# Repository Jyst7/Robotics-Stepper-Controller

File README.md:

# Robotics-Stepper-Controller

This project is a motor controller board and a cycloidal gearbox. It is designed around the esp32 s3 and can handle up to 6 nema 23's using dm542's.

## Main features

- ESP32 S3: allows for wifi and bluetooth connectivity aswell as allows programming using arduino ide

- up to 6 motors: allows for using up to 60 motors through the dm542 motor driver

- up to 8 inputs: allows for some electrically isolated inputs for limit switches probes, etc

- Sd card: not to sure what to use it for at the moment but its useful to have

- 3d printed cycloidal reducer: 1:10 ratio cycloidal gearbox designed to mount to a Keling KL23H276-30-4A stepper motor

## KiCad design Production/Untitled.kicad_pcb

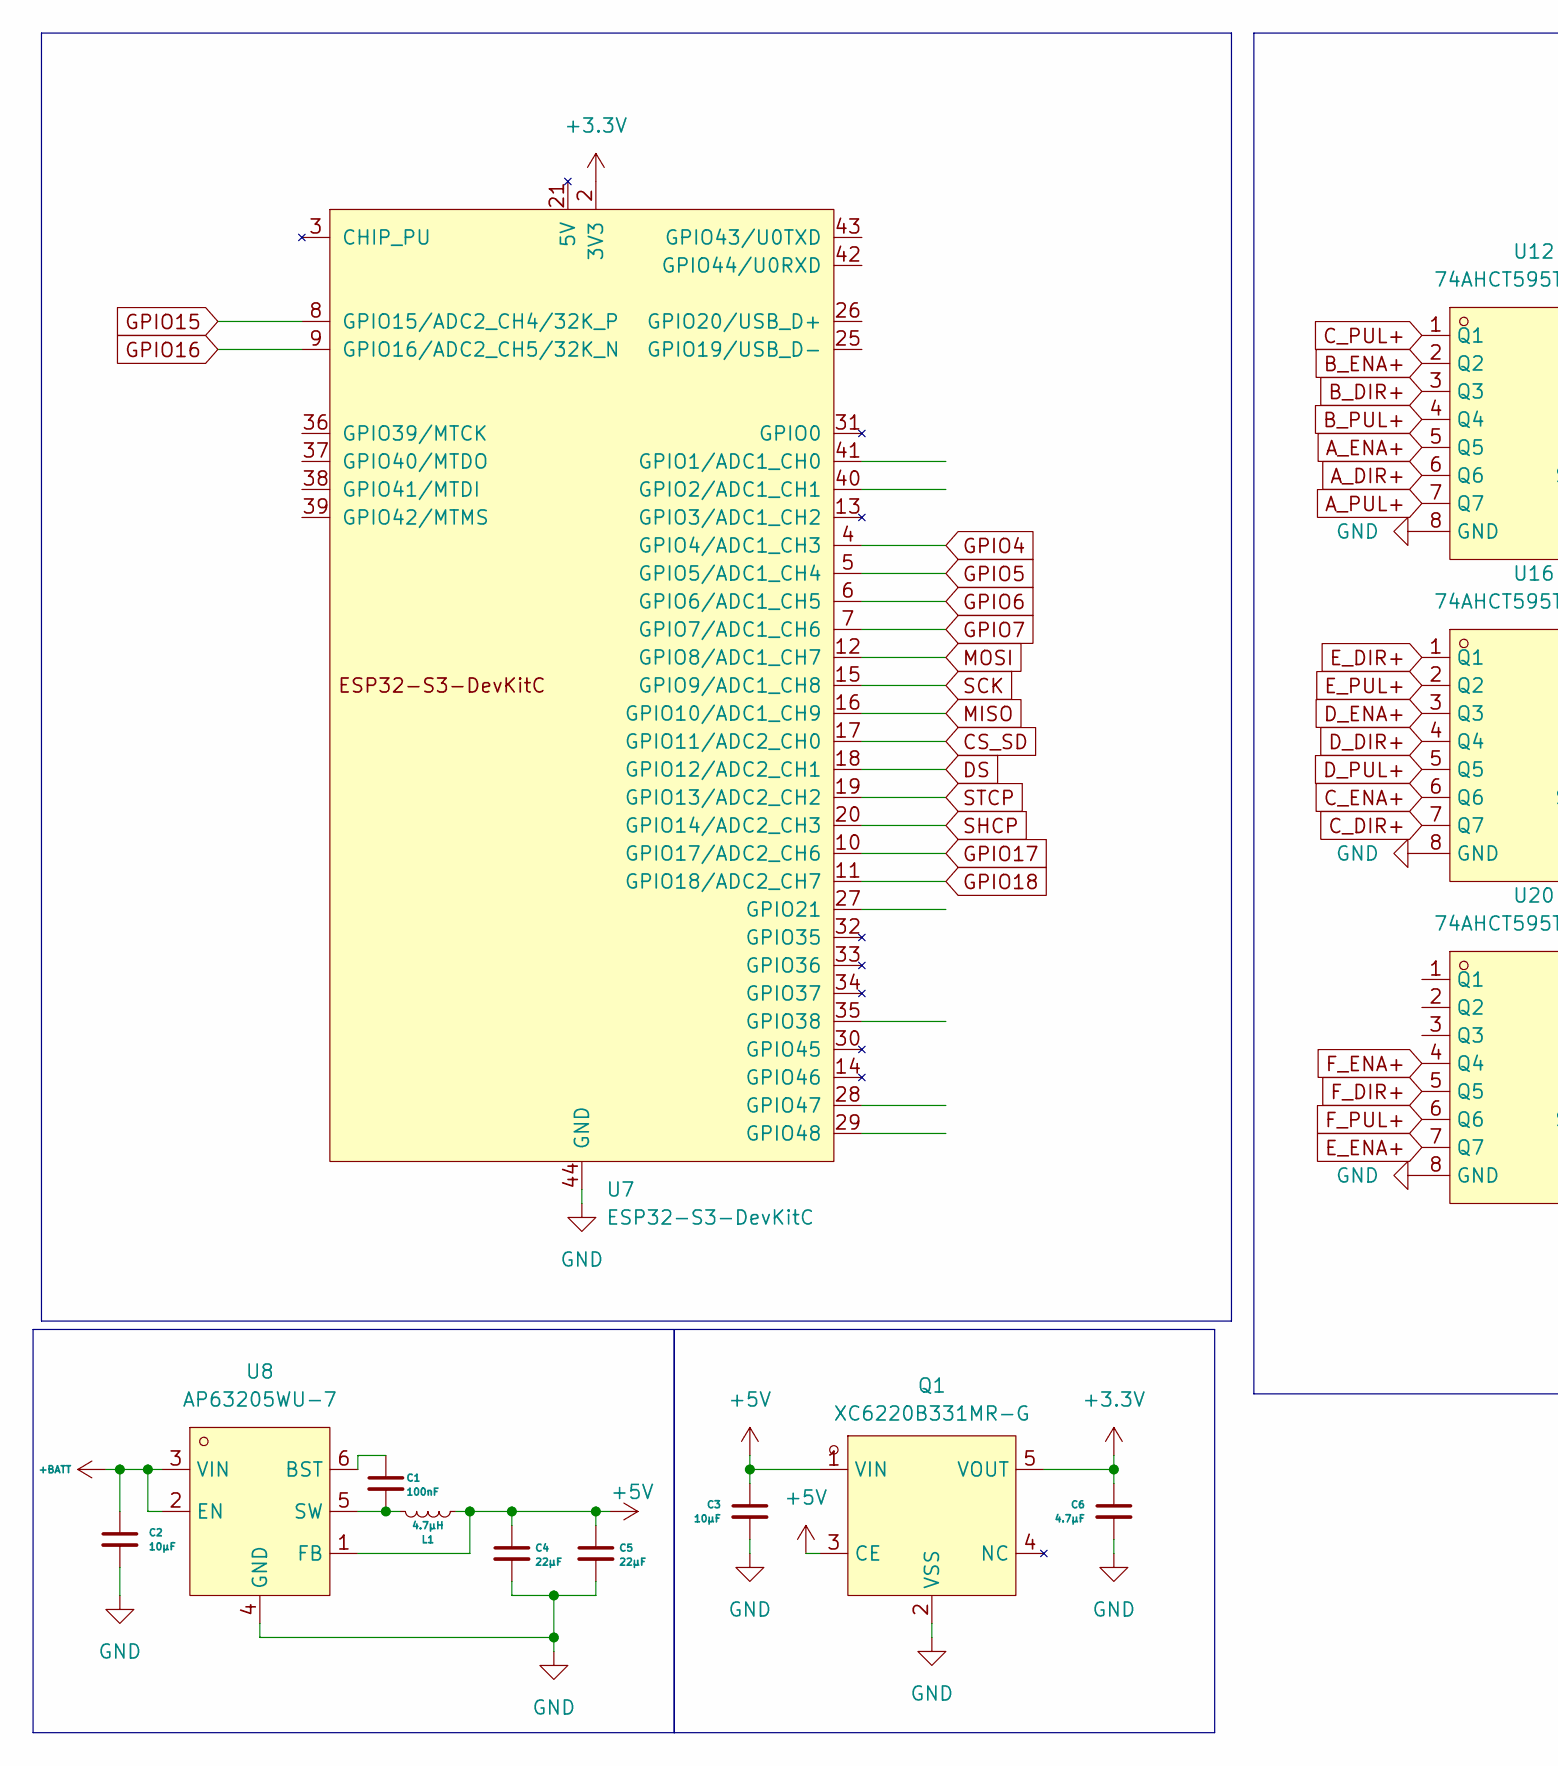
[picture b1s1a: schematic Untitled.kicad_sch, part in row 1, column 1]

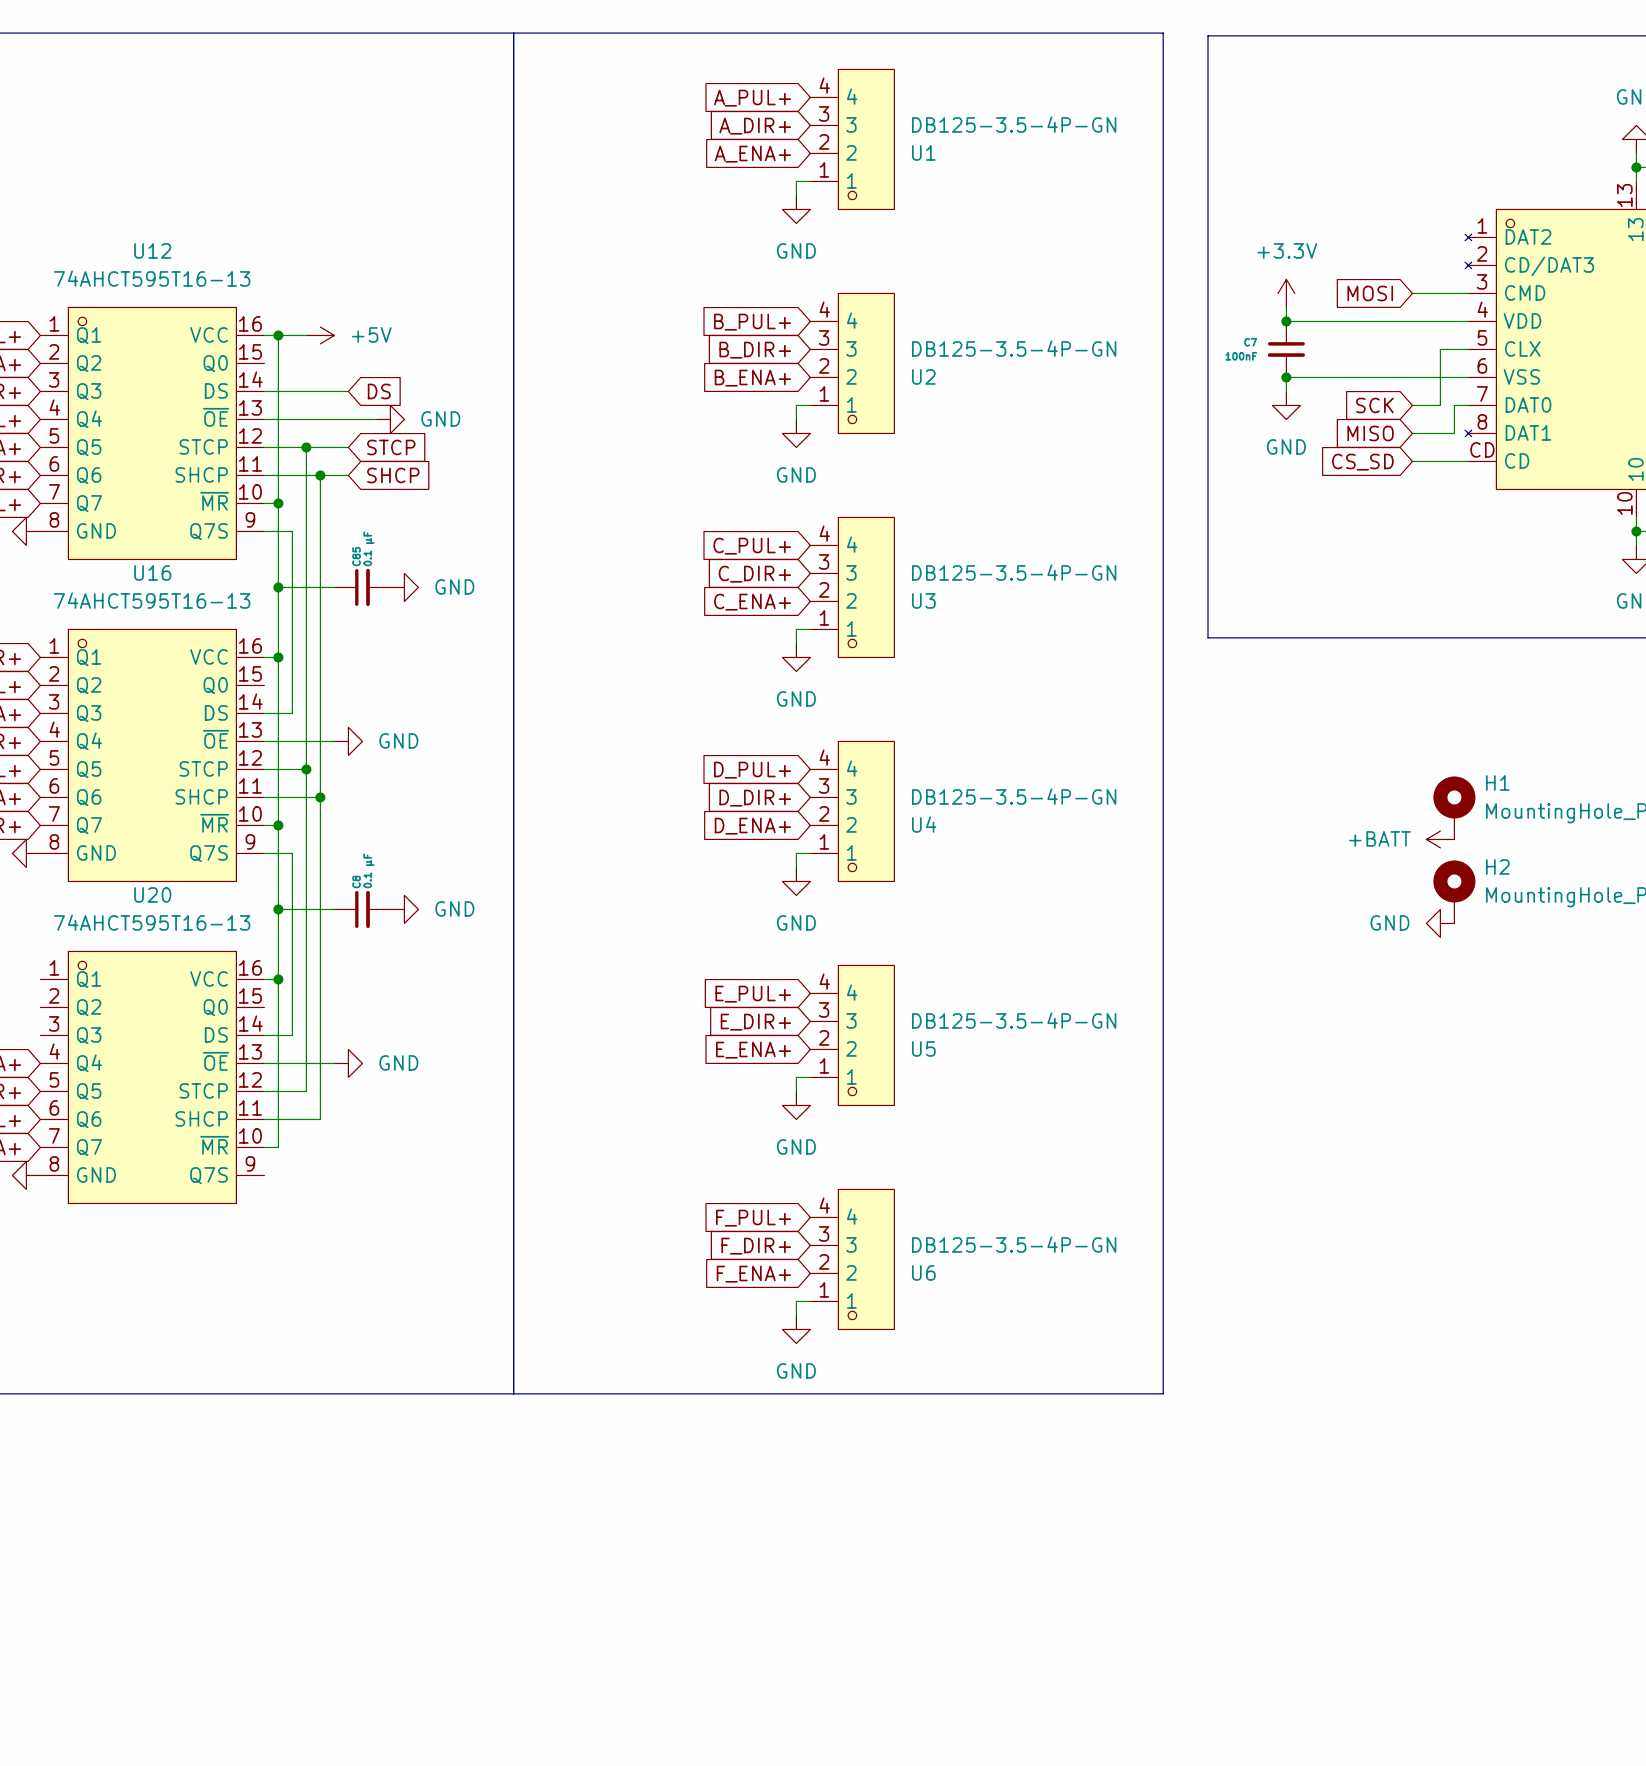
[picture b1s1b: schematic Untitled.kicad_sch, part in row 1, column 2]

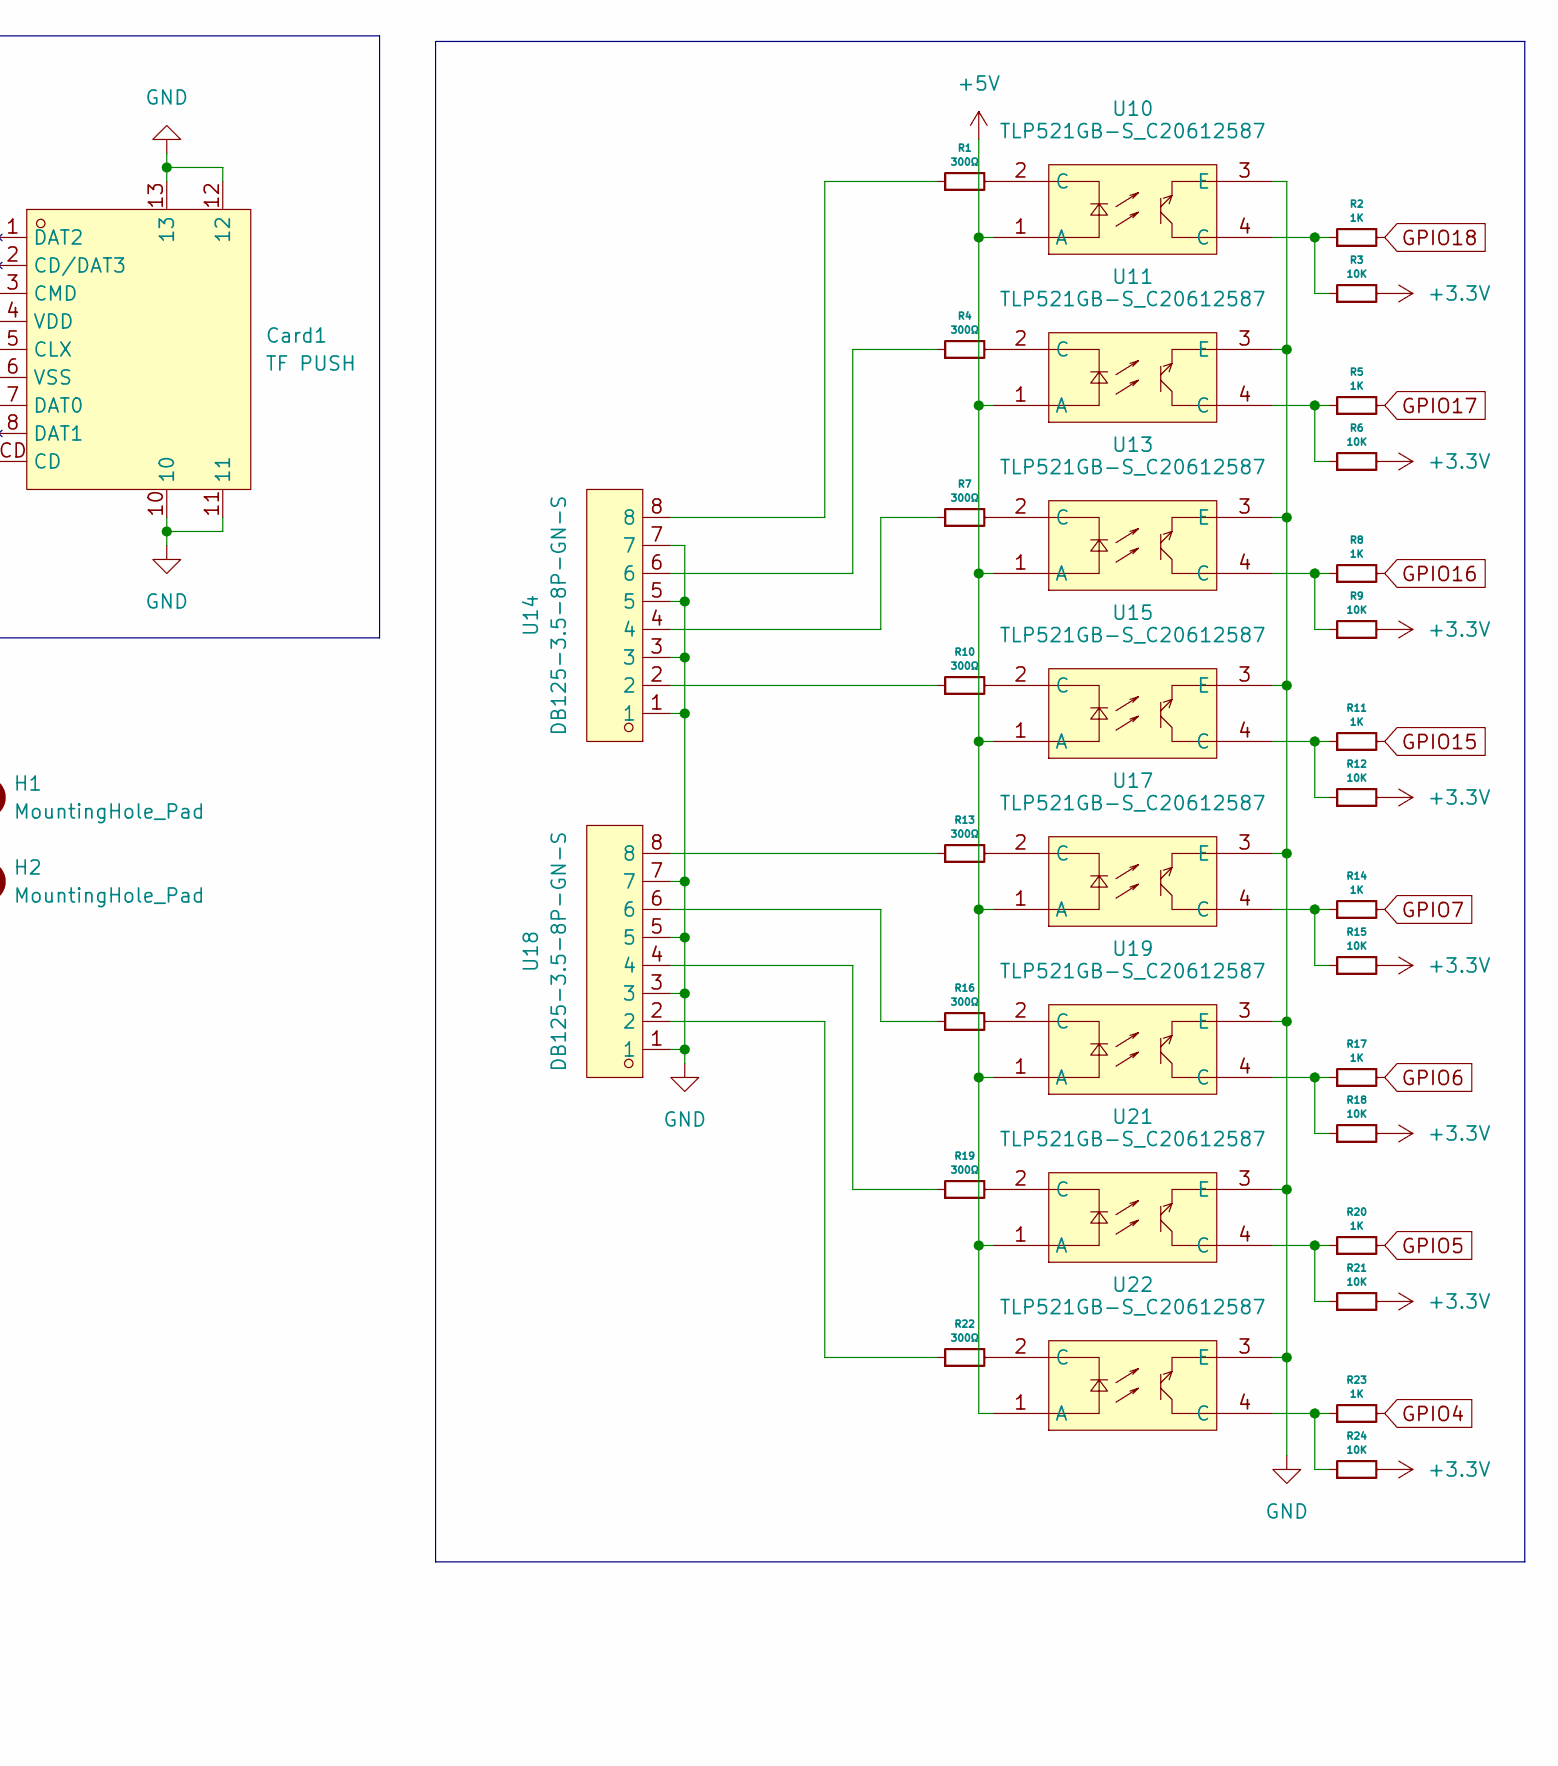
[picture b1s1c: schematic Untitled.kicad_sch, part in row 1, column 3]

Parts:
C1: 100nF; C_0805_2012Metric_Pad1.18x1.45mm_HandSolder
C2: 10μF; C_1206_3216Metric
C3: 10μF; C_0805_2012Metric_Pad1.18x1.45mm_HandSolder
C4, C5: 22μF; C_1206_3216Metric
C6: 4.7μF; C_0805_2012Metric_Pad1.18x1.45mm_HandSolder
C7: 100nF; C_1206_3216Metric
C8, C85: 0.1 μF; C_0805_2012Metric_Pad1.18x1.45mm_HandSolder
Card1: TF PUSH; TF-SMD_TF-PUSH; MPN TF PUSH; LCSC Part C393941
H1, H2: MountingHole_Pad; MountingHole_4.3x6.2mm_M4_Pad
L1: 4.7μH; IND-SMD_L5.0-W5.0
Q1: XC6220B331MR-G; SOT-25_L3.0-W1.6-P0.95-LS2.8-TL; MPN XC6220B331MR-G; LCSC Part C86534
R1, R4, R7, R10, R13, R16, R19, R22: 300Ω; R_0805_2012Metric_Pad1.20x1.40mm_HandSolder
R2, R5, R8, R11, R14, R17, R20, R23: 1K; R_0805_2012Metric_Pad1.20x1.40mm_HandSolder
R3, R6, R9, R12, R15, R18, R21, R24: 10K; R_0805_2012Metric_Pad1.20x1.40mm_HandSolder
U1, U2, U3, U4, U5, U6: DB125-3.5-4P-GN; CONN-TH_DB125-3.5-4P-GN; MPN DB125-3.5-4P-GN-S; LCSC Part C2757925
U7: ESP32-S3-DevKitC
U8: AP63205WU-7; TSOT-23-6_L2.9-W1.6-P0.95-LS2.8-BL; MPN AP63205WU-7; LCSC Part C2071056
U10, U11, U13, U15, U17, U19, U21, U22: TLP521GB-S_C20612587; SMD-4_L6.5-W4.6-P2.54-LS10.2-BL; MPN TLP521GB-S; LCSC Part C20612587
U12, U16, U20: 74AHCT595T16-13; TSSOP-16_L5.0-W4.4-P0.65-LS6.4-BL; MPN 74AHCT595T16-13; LCSC Part C460504
U14, U18: DB125-3.5-8P-GN-S; CONN-TH_8P-P3.50_DORABO_DB125-3.5-8P-GN-S; MPN DB125-3.5-8P-GN-S; LCSC Part C5184954

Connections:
+3.3V: C6.1, C7.1, Card1.4 (VDD), Q1.5 (VOUT), R3.2, R6.2, R9.2, R12.2, R15.2, R18.2, R21.2, R24.2, U7.1 (3V3), U7.2 (3V3)
+5V: C3.1, C4.1, C5.1, C8.1, C85.1, L1.2, Q1.1 (VIN), Q1.3 (CE), U8.1 (FB), U10.1 (A), U11.1 (A), U12.10 (~MR), U12.16 (VCC), U13.1 (A), U15.1 (A), U16.10 (~MR), U16.16 (VCC), U17.1 (A), U19.1 (A), U20.10 (~MR), U20.16 (VCC), U21.1 (A), U22.1 (A)
+BATT: C2.1, H1.1, U8.2 (EN), U8.3 (VIN)
A_DIR+: U1.3, U12.6 (Q6)
A_ENA+: U1.2, U12.5 (Q5)
A_PUL+: U1.4, U12.7 (Q7)
B_DIR+: U2.3, U12.3 (Q3)
B_ENA+: U2.2, U12.2 (Q2)
B_PUL+: U2.4, U12.4 (Q4)
CS_SD: Card1.CD, U7.17 (GPIO11/ADC2_CH0)
C_DIR+: U3.3, U16.7 (Q7)
C_ENA+: U3.2, U16.6 (Q6)
C_PUL+: U3.4, U12.1 (Q1)
DS: U7.18 (GPIO12/ADC2_CH1), U12.14 (DS)
D_DIR+: U4.3, U16.4 (Q4)
D_ENA+: U4.2, U16.3 (Q3)
D_PUL+: U4.4, U16.5 (Q5)
E_DIR+: U5.3, U16.1 (Q1)
E_ENA+: U5.2, U20.7 (Q7)
E_PUL+: U5.4, U16.2 (Q2)
F_DIR+: U6.3, U20.5 (Q5)
F_ENA+: U6.2, U20.4 (Q4)
F_PUL+: U6.4, U20.6 (Q6)
GND: C2.2, C3.2, C4.2, C5.2, C6.2, C7.2, C8.2, C85.2, Card1.6 (VSS), Card1.10, Card1.11, Card1.12, Card1.13, H2.1, Q1.2 (VSS), U1.1, U2.1, U3.1, U4.1, U5.1, U6.1, U7.22 (GND), U7.23 (GND), U7.24 (GND), U7.44 (GND), U8.4 (GND), U10.3 (E), U11.3 (E), U12.8 (GND), U12.13 (~OE), U13.3 (E), U14.1, U14.3, U14.5, U14.7, U15.3 (E), U16.8 (GND), U16.13 (~OE), U17.3 (E), U18.1, U18.3, U18.5, U18.7, U19.3 (E), U20.8 (GND), U20.13 (~OE), U21.3 (E), U22.3 (E)
GPIO4: R23.2, U7.4 (GPIO4/ADC1_CH3)
GPIO5: R20.2, U7.5 (GPIO5/ADC1_CH4)
GPIO6: R17.2, U7.6 (GPIO6/ADC1_CH5)
GPIO7: R14.2, U7.7 (GPIO7/ADC1_CH6)
GPIO15: R11.2, U7.8 (GPIO15/ADC2_CH4/32K_P)
GPIO16: R8.2, U7.9 (GPIO16/ADC2_CH5/32K_N)
GPIO17: R5.2, U7.10 (GPIO17/ADC2_CH6)
GPIO18: R2.2, U7.11 (GPIO18/ADC2_CH7)
MISO: Card1.7 (DAT0), U7.16 (GPIO10/ADC1_CH9)
MOSI: Card1.3 (CMD), U7.12 (GPIO8/ADC1_CH7)
unnamed: R1.1, U14.8
unnamed: R1.2, U10.2 (C)
unnamed: R2.1, R3.1, U10.4 (C)
unnamed: R4.1, U14.6
unnamed: R4.2, U11.2 (C)
unnamed: R5.1, R6.1, U11.4 (C)
unnamed: R7.1, U14.4
unnamed: R7.2, U13.2 (C)
unnamed: R8.1, R9.1, U13.4 (C)
unnamed: R10.1, U14.2
unnamed: R10.2, U15.2 (C)
unnamed: R11.1, R12.1, U15.4 (C)
unnamed: R13.1, U18.8
unnamed: R13.2, U17.2 (C)
unnamed: R14.1, R15.1, U17.4 (C)
unnamed: R16.1, U18.6
unnamed: R16.2, U19.2 (C)
unnamed: R17.1, R18.1, U19.4 (C)
unnamed: R19.1, U18.4
unnamed: R19.2, U21.2 (C)
unnamed: R20.1, R21.1, U21.4 (C)
unnamed: R22.1, U18.2
unnamed: R22.2, U22.2 (C)
unnamed: R23.1, R24.1, U22.4 (C)
unnamed: C1.1, U8.6 (BST)
unnamed: C1.2, L1.1, U8.5 (SW)
unnamed: U12.9 (Q7S), U16.14 (DS)
unnamed: U16.9 (Q7S), U20.14 (DS)
SCK: Card1.5 (CLX), U7.15 (GPIO9/ADC1_CH8)
SHCP: U7.20 (GPIO14/ADC2_CH3), U12.11 (SHCP), U16.11 (SHCP), U20.11 (SHCP)
STCP: U7.19 (GPIO13/ADC2_CH2), U12.12 (STCP), U16.12 (STCP), U20.12 (STCP)

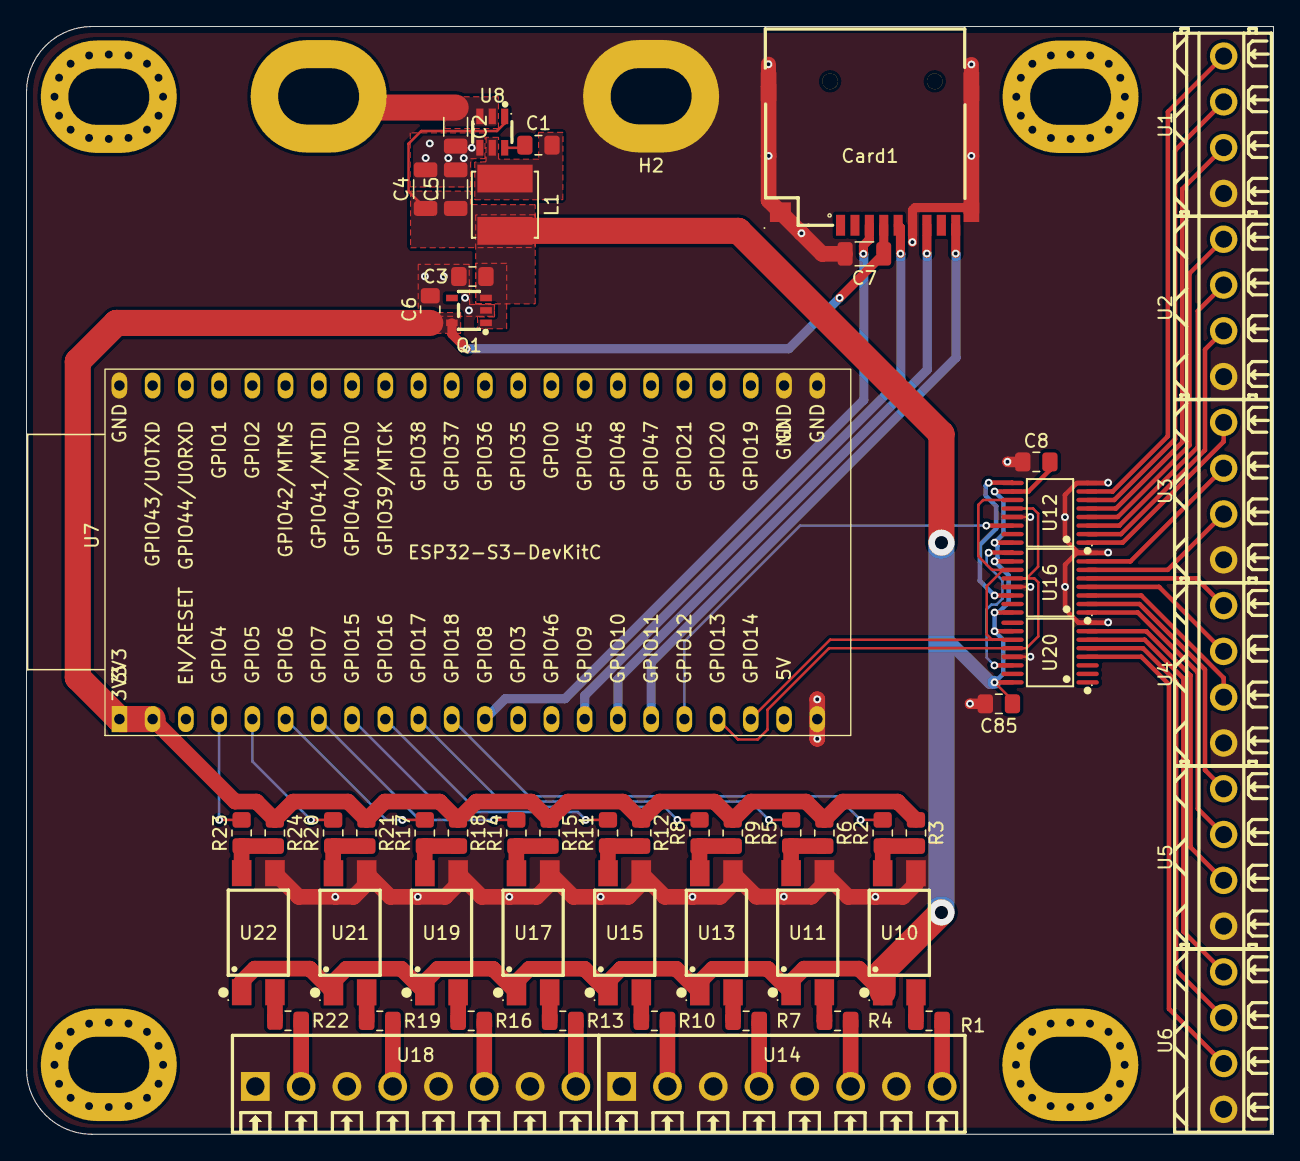
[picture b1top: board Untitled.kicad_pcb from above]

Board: 2 copper layers, 95.3 x 84.7 mm, 59 parts (1 on the bottom side), 65 nets.

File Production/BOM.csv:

Untitled,,,,,,,,,
Reference,Qty,Value,DNP,Exclude from BOM,Exclude from Board,Footprint,Datasheet,LCSC Part,Price
"U14,U18",2,DB125-3.5-8P-GN-S,,,,easyeda2kicad:CONN-TH_8P-P3.50_DORABO_DB125-3.5-8P-GN-S,https://www.lcsc.com/datasheet/C5184954.pdf,C5184954,$1.30
"U12,U16,U20",5,74AHCT595T16-13,,,,easyeda2kicad:TSSOP-16_L5.0-W4.4-P0.65-LS6.4-BL,https://lcsc.com/product-detail/presales_Diodes-Incorporated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,C460504,$1.32
"U10,U11,U13,U15,U17,U19,U21,U22",10,TLP521GB-S_C20612587,,,,easyeda2kicad:SMD-4_L6.5-W4.6-P2.54-LS10.2-BL,https://www.lcsc.com/datasheet/C20612587.pdf,C20612587,$1.10
U8,1,AP63205WU-7,,,,easyeda2kicad:TSOT-23-6_L2.9-W1.6-P0.95-LS2.8-BL,https://www.lcsc.com/datasheet/C2071056.pdf,C2071056,$0.44
U7,5,ESP32-S3-DevKitC(PIN HEADERS),,,,PCM_Espressif:ESP32-S3-DevKitC,https://www.lcsc.com/datasheet/C7499337.pdf,C7499337,$0.93
"U1,U2,U3,U4,U5,U6",10,DB125-3.5-4P-GN,,,,easyeda2kicad:CONN-TH_DB125-3.5-4P-GN,https://www.lcsc.com/datasheet/C2757925.pdf,C2757925,$3.37
"R3,R6,R9,R12,R15,R18,R21,R24",20,10K,,,,Resistor_SMD:R_0805_2012Metric_Pad1.20x1.40mm_HandSolder,https://www.lcsc.com/datasheet/C110775.pdf,C110775,$0.78
"R2,R5,R8,R11,R14,R17,R20,R23",20,1K,,,,Resistor_SMD:R_0805_2012Metric_Pad1.20x1.40mm_HandSolder,https://www.lcsc.com/datasheet/C110774.pdf,C110774,$0.79
"R1,R4,R7,R10,R13,R16,R19,R22",10,300Ω,,,,Resistor_SMD:R_0805_2012Metric_Pad1.20x1.40mm_HandSolder,https://www.lcsc.com/datasheet/C7603206.pdf,C7603206,$3.45
Q1,1,XC6220B331MR-G,,,,easyeda2kicad:SOT-25_L3.0-W1.6-P0.95-LS2.8-TL,https://lcsc.com/product-detail/Low-Dropout-Regulators-LDO_X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,C86534,$0.45
L1,10,4.7μH,,,,easyeda2kicad:IND-SMD_L5.0-W5.0,https://www.lcsc.com/datasheet/C520348.pdf,C520348,$0.56
Card1,10,TF PUSH,,,,easyeda2kicad:TF-SMD_TF-PUSH,https://lcsc.com/product-detail/Connector-Card-Sockets_SHOU-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,C393941,$1.26
"C1,C7,C8,C85",50,0.1 μF,,,,Capacitor_SMD:C_0805_2012Metric_Pad1.18x1.45mm_HandSolder,https://www.lcsc.com/datasheet/C49678.pdf,C49678,$1.34
C7,50,100nF,,,,Capacitor_SMD:C_1206_3216Metric,https://www.lcsc.com/datasheet/C309030.pdf,C309030,$1.28
C6,10,4.7μF,,,,Capacitor_SMD:C_0805_2012Metric_Pad1.18x1.45mm_HandSolder,https://www.lcsc.com/datasheet/C33546011.pdf,C33546011,$0.78
"C4,C5",10,22μF,,,,Capacitor_SMD:C_1206_3216Metric,https://www.lcsc.com/datasheet/C342620.pdf,C342620,$3.61
"C2,C3",20,10μF,,,,Capacitor_SMD:C_0805_2012Metric_Pad1.18x1.45mm_HandSolder,https://www.lcsc.com/datasheet/C1713.pdf,C1713,$0.98

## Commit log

2026-06-18 stuff
2026-06-18 wrote stuff
2026-06-18 wrote more
2026-06-18 more
2026-06-18 werote
2026-06-21 asdf
2026-06-21 did stuff
2026-06-21 Enhance README with image and actuator details
    Added an image and additional context about the cycloidal actuator.
2026-06-21 Update README with project details and features
    Expanded project description and added main features section.
2026-06-24 Update screenshot in README.md
    Replaced an image in the README with a new screenshot.
2026-06-24 everything
